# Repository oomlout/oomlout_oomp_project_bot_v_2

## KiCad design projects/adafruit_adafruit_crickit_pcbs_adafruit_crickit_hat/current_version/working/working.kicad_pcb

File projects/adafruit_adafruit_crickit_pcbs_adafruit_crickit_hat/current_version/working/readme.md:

# adafruit_crickit_pcbs
 
## summary 
* id: adafruit_adafruit_crickit_pcbs_adafruit_crickit_hat
* user: adafruit
* name: adafruit_crickit_pcbs
* board: adafruit_crickit_hat
* repo: https://github.com/adafruit/Adafruit_Crickit_PCBs

* src_file_repo_sch: 
* src_file_repo_sch_link: https://github.com/adafruit/Adafruit_Crickit_PCBs/tree/master/
* full details link: https://github.com/oomlout/oomlout_oomp_project_bot_v_2/tree/main/projects/adafruit_adafruit_crickit_pcbs_adafruit_crickit_hat/current_version/working  

## schematic  
  
[schematic (pdf)](working_schematic.pdf) 

## pcb  

[board (pdf)](working.pdf)  

## working_bom
| Id | Designator | Footprint | Quantity | Designation | Supplier and ref |  | None | 
| --- | --- | --- | --- | --- | --- | --- | --- | 
| 1 | C12,C6,C20,C22,C11,C18 | 0805-NO | 6 | 0.1uF |  |  | [''] | 
| 2 | JP8 | TERMBLOC_1X5-3.5MM | 1 | 5pin 3.5mm |  |  | [''] | 
| 3 | R9,R10 | 0603-NO | 2 | 1Mohm |  |  | [''] | 
| 4 | TP31,TP30,TP32,TP29 | PCB_ALLI | 4 | SEWTAPPCB_ALLIGATOR |  |  | [''] | 
| 5 | SPKR0 | TERMBLOCK_1X2-3.5MM | 1 | 3.5mm |  |  | [''] | 
| 6 | R16,R17,R11,R8,R1 | 0603-NO | 5 | 264K |  |  | [''] | 
| 7 | R12,R13 | 0805-NO | 2 | 100 |  |  | [''] | 
| 8 | POWERFAIL0 | CHIPLED_0805_NOOUTLINE | 1 | red |  |  | [''] | 
| 9 | VR2 | TRIMPOT_BOURNS_3303W | 1 | 10K trim |  |  | [''] | 
| 10 | POWEROK0 | CHIPLED_0805_NOOUTLINE | 1 | green |  |  | [''] | 
| 11 | MS2 | FEATHERWING_SMT2 | 1 | FEATHERWING_SMTDUAL |  |  | [''] | 
| 12 | CN1 | 4UCONN_20329_V2 | 1 | 4U#20329 |  |  | [''] | 
| 13 | C10 | PANASONIC_C | 1 | 47uF+/16v |  |  | [''] | 
| 14 | R7,R2,R5,R18,R6,R15 | 0603-NO | 6 | 2.2K |  |  | [''] | 
| 15 | U2 | HTSSOP16 | 1 | DRV8833PWPR |  |  | [''] | 
| 16 | U$41,U$50,U$49,U$52,U$44,U$43,U$42,U$51 | MOUNTINGHOLE_3.0_NPH | 8 | MOUNTINGHOLE3.0_NPH |  |  | [''] | 
| 17 | FB1 | 0805-NO | 1 | Ferrite |  |  | [''] | 
| 18 | C17,C19,C7,C15,C2,C16,C21 | 0805-NO | 7 | 10uF |  |  | [''] | 
| 19 | IC4 | WSON8 | 1 | TPS259573 |  |  | [''] | 
| 20 | C8 | 0603-NO | 1 | DNP |  |  | [''] | 
| 21 | C3 | 0805_10MGAP | 1 | 1uF |  |  | [''] | 
| 22 | Q2 | POWERDI3333 | 1 | AON7401 |  |  | [''] | 
| 23 | R4,R3 | _1206 | 2 | 0.2Î© |  |  | [''] | 
| 24 | U5 | MSOP8_0.65MM | 1 | PAM8302AASCR |  |  | [''] | 
| 25 | JP2 | TERMBLOC_1X5-3.5MM | 1 | 3.5mm |  |  | [''] | 
| 26 | D1,D2 | SOD-323 | 2 | 1N4148 |  |  | [''] | 
| 27 | C13,C14 | 0805-NO | 2 | 1uF |  |  | [''] | 
| 28 | FID1,FID3,FID2 | FIDUCIAL_1MM | 3 | FIDUCIAL_1MM |  |  | [''] | 
| 29 | X2 | DCJACK_2MM_PTH | 1 | 2.1mm DC |  |  | [''] | 
| 30 | JP5 | 1X01_ROUND | 1 |  |  |  | [''] | 
| 31 | IC2 | SO16 | 1 | ULN2003AD |  |  | [''] | 
| 32 | L0 | CHIPLED_0805_NOOUTLINE | 1 | yellow |  |  | [''] | 
| 33 | C5 | 0805-NO | 1 | 10ÂµF |  |  | [''] | 
| 34 | ON/OFF0 | EG1390 | 1 | MSS-22C01G2 |  |  | [''] | 
| 35 | SJ1 | SOLDERJUMPER_CLOSEDWIRE | 1 |  |  |  | [''] | 
| 36 | LED1 | LED3535 | 1 | WS2812B3535 |  |  | [''] | 
| 37 | GPIO0 | 3X08 | 1 | 3x8 FEMALE |  |  | [''] | 
| 38 | JP3 | 1X16_ROUND | 1 |  |  |  | [''] | 
| 39 | U$4 | TQFN48_7MM | 1 | ATSAMD21G_QFN |  |  | [''] | 
| 40 | IC3 | SOT23-5 | 1 | 74AHCT1G125DBV |  |  | [''] | 
| 41 | U$74 | CRICKIT_WING_TOP | 1 |  |  |  | [''] | 
| 42 | SERVO0 | 3X04 | 1 | 3x4 Male |  |  | [''] | 
| 43 | C4,C1 | 0805-NO | 2 | 10ÂµF/16V |  |  | [''] | 
| 44 | JP1 | 1X02_ROUND | 1 |  |  |  | [''] | 
| 45 | C9 | PANASONIC_C | 1 | 47uF/16v |  |  | [''] | 
| 46 | R14 | 0603-NO | 1 | 510 |  |  | [''] | 
| 47 | U1 | SOT23-5 | 1 | mic5225-3.3 |  |  | [''] | 
| 48 | SW1 | EVQ-Q2_SMALLER | 1 | EVQQ2 |  |  | [''] | 
| 49 | JP4 | 1X12_ROUND | 1 |  |  |  | [''] | 
| 50 | NEOPIX0 | TERMBLOCK_1X3-3.5MM | 1 | 3.5mm |  |  | [''] | 
| 51 | SJ8 | SOLDERJUMPER_ARROW_NOPASTE | 1 | ISENSEB |  |  | [''] | 
| 52 | TP3,TP1,TP2 | TP15R | 3 | TPTP15R |  |  | [''] | 
| 53 | U$72 | CRICKIT_WING_BOT | 1 |  |  |  | [''] | 
| 54 | U$76 | PCBFEAT-REV-040 | 1 |  |  |  | [''] | 
| 55 | SJ7 | SOLDERJUMPER_ARROW_NOPASTE | 1 | ISENSEA |  |  | [''] | 

## bom_schematic
no data

## mounting_holes
| x | y | package | value | ref | size | 
| --- | --- | --- | --- | --- | --- | 
| 21.59 | 0.0 | MOUNTINGHOLE_3.0_NPH | MOUNTINGHOLE3.0_NPH | U$41 | m3 | 
| 53.85 | 0.0 | MOUNTINGHOLE_3.0_NPH | MOUNTINGHOLE3.0_NPH | U$42 | m3 | 
| 0.0 | 21.59 | MOUNTINGHOLE_3.0_NPH | MOUNTINGHOLE3.0_NPH | U$43 | m3 | 
| 75.44 | 21.59 | MOUNTINGHOLE_3.0_NPH | MOUNTINGHOLE3.0_NPH | U$44 | m3 | 
| 75.44 | 53.85 | MOUNTINGHOLE_3.0_NPH | MOUNTINGHOLE3.0_NPH | U$49 | m3 | 
| 0.0 | 53.85 | MOUNTINGHOLE_3.0_NPH | MOUNTINGHOLE3.0_NPH | U$50 | m3 | 
| 21.59 | 75.44 | MOUNTINGHOLE_3.0_NPH | MOUNTINGHOLE3.0_NPH | U$51 | m3 | 
| 53.85 | 75.44 | MOUNTINGHOLE_3.0_NPH | MOUNTINGHOLE3.0_NPH | U$52 | m3 |

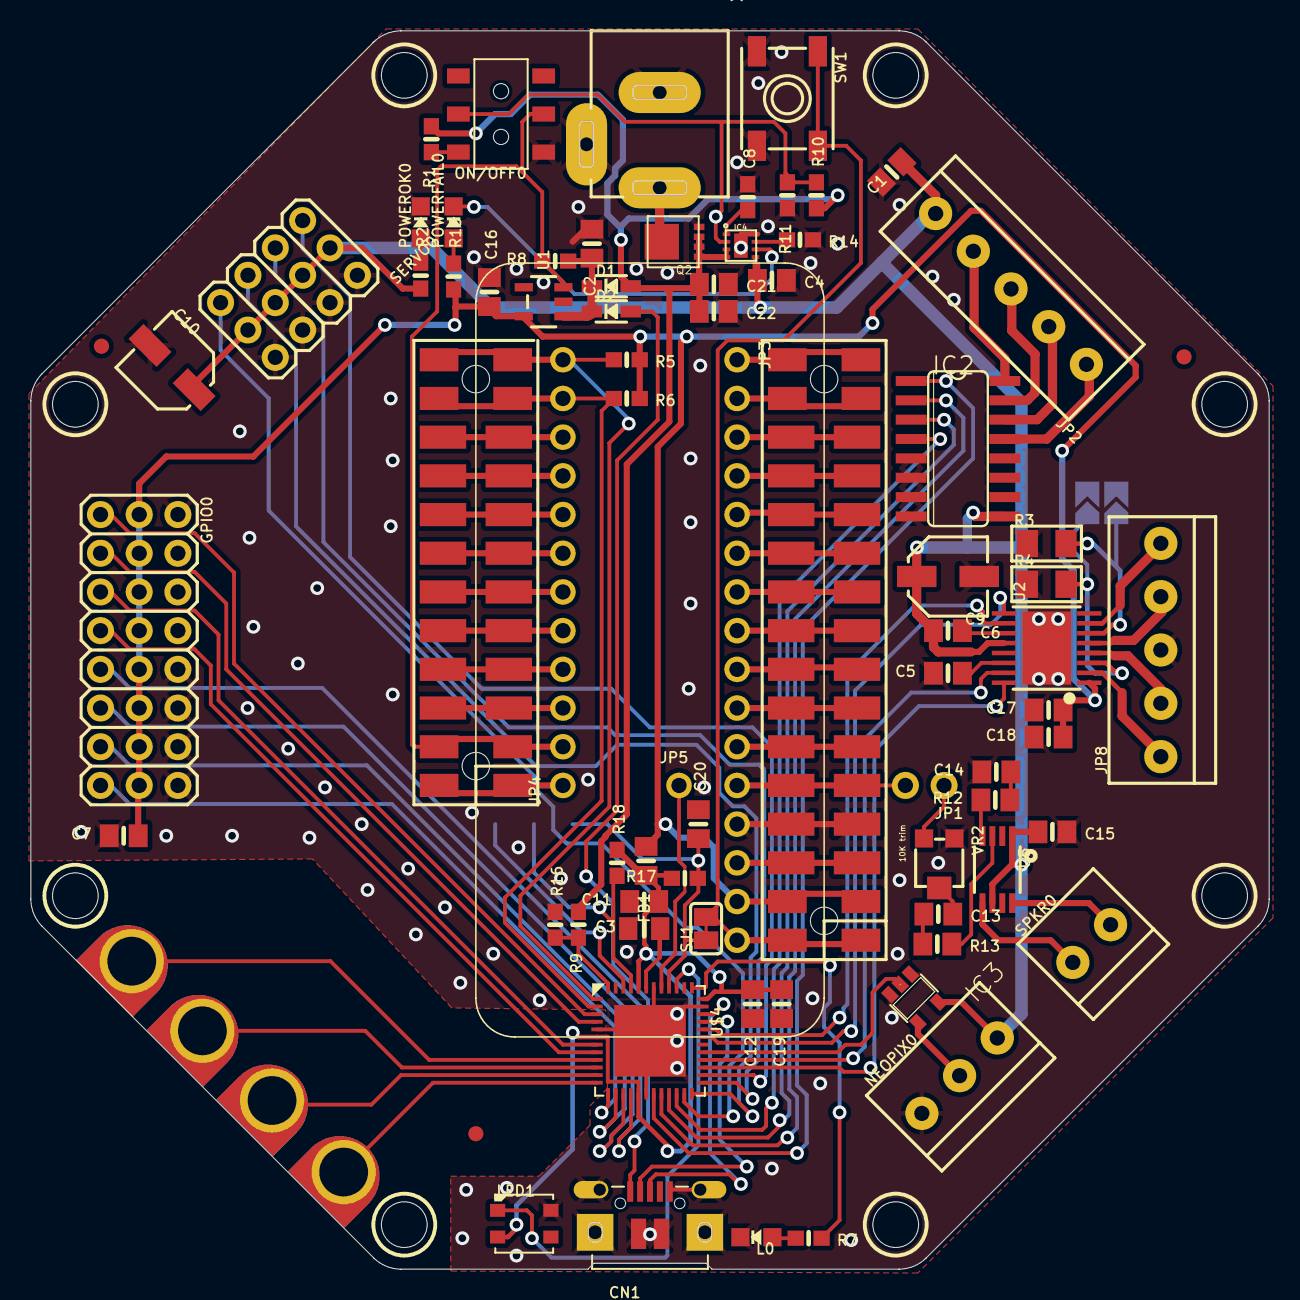
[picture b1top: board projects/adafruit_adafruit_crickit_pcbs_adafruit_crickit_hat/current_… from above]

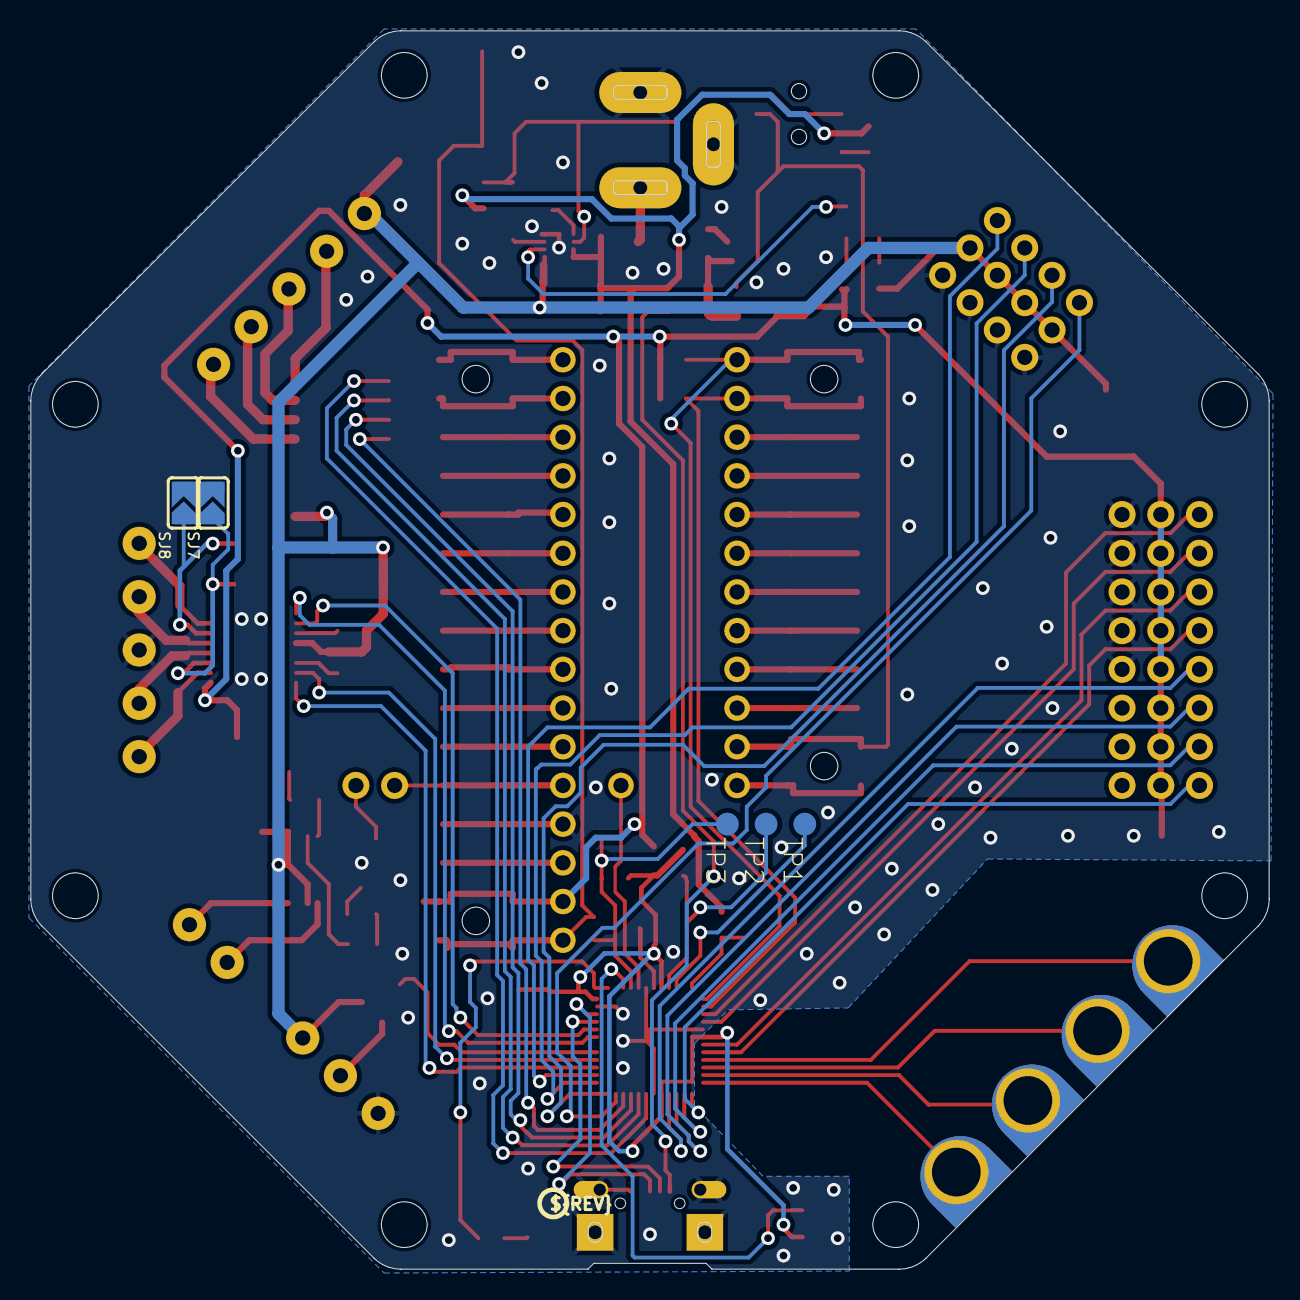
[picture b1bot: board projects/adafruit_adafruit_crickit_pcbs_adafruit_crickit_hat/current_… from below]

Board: 16 copper layers, 81.3 x 81.3 mm, 95 parts (7 on the bottom side), 98 nets.

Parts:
C1, C4: 10µF/16V; 0805-NO
C2, C7, C15, C16, C17, C19, C21: 10uF; 0805-NO
C3: 1uF; 0805_10MGAP
C5: 10µF; 0805-NO
C6, C11, C12, C18, C20, C22: 0.1uF; 0805-NO
C8: DNP; 0603-NO
C9: 47uF/16v; PANASONIC_C
C10: 47uF+/16v; PANASONIC_C
C13, C14: 1uF; 0805-NO
CN1: 4U#20329; 4UCONN_20329_V2
D1, D2: 1N4148; SOD-323
FB1: Ferrite; 0805-NO
FID1, FID2, FID3: FIDUCIAL_1MM
GPIO0: 3x8 FEMALE; 3X08
IC2: ULN2003AD; SO16
IC3: 74AHCT1G125DBV; SOT23-5
IC4: TPS259573; WSON8
JP1: 1X02_ROUND
JP2: 3.5mm; TERMBLOC_1X5-3.5MM
JP3: 1X16_ROUND
JP4: 1X12_ROUND
JP5: 1X01_ROUND
JP8: 5pin 3.5mm; TERMBLOC_1X5-3.5MM
L0: yellow; CHIPLED_0805_NOOUTLINE
LED1: WS2812B3535; LED3535
MS2: FEATHERWING_SMTDUAL; FEATHERWING_SMT2
NEOPIX0: 3.5mm; TERMBLOCK_1X3-3.5MM
ON/OFF0: MSS-22C01G2; EG1390
POWERFAIL0: red; CHIPLED_0805_NOOUTLINE
POWEROK0: green; CHIPLED_0805_NOOUTLINE
Q2: AON7401; POWERDI3333
R1, R8, R11, R16, R17: 264K; 0603-NO
R2, R5, R6, R7, R15, R18: 2.2K; 0603-NO
R3, R4: 0.2Ω; _1206
R9, R10: 1Mohm; 0603-NO
R12, R13: 100; 0805-NO
R14: 510; 0603-NO
SERVO0: 3x4 Male; 3X04
SJ1: SOLDERJUMPER_CLOSEDWIRE
SJ7: ISENSEA; SOLDERJUMPER_ARROW_NOPASTE
SJ8: ISENSEB; SOLDERJUMPER_ARROW_NOPASTE
SPKR0: 3.5mm; TERMBLOCK_1X2-3.5MM
SW1: EVQQ2; EVQ-Q2_SMALLER
TP1, TP2, TP3: TPTP15R; TP15R
TP29, TP30, TP31, TP32: SEWTAPPCB_ALLIGATOR; PCB_ALLI
U1: mic5225-3.3; SOT23-5
U2: DRV8833PWPR; HTSSOP16
U5: PAM8302AASCR; MSOP8_0.65MM
U$4: ATSAMD21G_QFN; TQFN48_7MM
U$41, U$42, U$43, U$44, U$49, U$50, U$51, U$52: MOUNTINGHOLE3.0_NPH; MOUNTINGHOLE_3.0_NPH
U$72: CRICKIT_WING_BOT
U$74: CRICKIT_WING_TOP
U$76: PCBFEAT-REV-040
VR2: 10K trim; TRIMPOT_BOURNS_3303W
X2: 2.1mm DC; DCJACK_2MM_PTH

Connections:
3.3V: C7.1, C16.1, C17.1, C18.1, FB1.1, GPIO0.2, GPIO0.5, GPIO0.8, GPIO0.11, GPIO0.14, GPIO0.17, GPIO0.20, GPIO0.23, JP3.15, MS2.2, MS2.2', R5.2, R6.2, R15.1, U1.5, U2.1
5.0V: C1.1, C4.1, C6.1, C9.+, C10.+, C15.1, IC2.9, IC3.5, IC4.5, JP2.P5, NEOPIX0.1, R2.1, SERVO0.2, SERVO0.5, SERVO0.8, SERVO0.11, U2.12, U5.1, U5.6
ANALOG1: GPIO0.1, U$4.3
ANALOG2: GPIO0.4, U$4.4
ANALOG3: GPIO0.7, U$4.7
ANALOG4: GPIO0.10, U$4.8
ANALOG5: GPIO0.13, U$4.16
ANALOG6: GPIO0.16, U$4.15
ANALOG7: GPIO0.19, U$4.14
ANALOG8: GPIO0.22, U$4.13
AOUT3: JP8.P1, U2.2
AOUT4: JP8.P2, U2.4
AREF: JP3.14, MS2.3, MS2.3'
AUDIO: JP1.1, VR2.3
AUDIO_OUT: JP1.2, JP3.12, MS2.5, MS2.5'
B: JP3.11, MS2.6, MS2.6'
C: JP3.10, MS2.7, MS2.7'
CAPTOUCH1: TP30.P$1, U$4.9
CAPTOUCH2: TP32.P$1, U$4.10
CAPTOUCH3: TP29.P$1, U$4.11
CAPTOUCH4: TP31.P$1, U$4.12
D: JP3.9, MS2.8, MS2.8'
D+: CN1.D+, U$4.34
D-: CN1.D-, U$4.33
DRIVEIN1: IC2.1, U$4.19
DRIVEIN2: IC2.2, U$4.20
DRIVEIN3: IC2.3, U$4.21
DRIVEIN4: IC2.4, U$4.22
DRIVEOUT1: IC2.16, JP2.P4
DRIVEOUT2: IC2.15, JP2.P3
DRIVEOUT3: IC2.14, JP2.P2
DRIVEOUT4: IC2.13, JP2.P1
E: JP3.8, MS2.9, MS2.9'
ENABLE: JP4.2, MS2.27, MS2.27', ON/OFF0.P2, R8.2, U1.3
F: JP3.7, MS2.10, MS2.10'
G: JP3.1, MS2.16, MS2.16'
GND: C1.2, C2.1, C3.2, C4.2, C5.2, C7.2, C8.2, C9.-, C10.-, C11.2, C12.2, C14.2, C15.2, C16.2, C17.2, C18.2, C19.2, C20.2, C21.2, C22.2, CN1.BASE@1, CN1.BASE@2, CN1.GND, CN1.SPRT@1, CN1.SPRT@2, CN1.SPRT@3, CN1.SPRT@4, GPIO0.3, GPIO0.6, GPIO0.9, GPIO0.12, GPIO0.15, GPIO0.18, GPIO0.21, GPIO0.24, IC2.5, IC2.6, IC2.7, IC2.8, IC3.1, IC3.3, IC4.8, IC4.PAD, JP3.13, JP8.P3, L0.C, LED1.4, MS2.4, MS2.4', NEOPIX0.3, ON/OFF0.O2, POWEROK0.C, Q2.4, R3.1, R4.1, R11.2, R14.2, R16.2, SERVO0.3, SERVO0.6, SERVO0.9, SERVO0.12, SJ7.2, SJ8.2, SW1.A, SW1.A', U1.2, U2.13, U2.PPAD, U5.7, U$4.5, U$4.18, U$4.35, U$4.42, U$4.THERMAL, VR2.1, X2.GND, X2.GNDBREAK
INT_NEO: LED1.1, U$4.39
IRQ: JP5.1, U$4.41
L: JP4.6, MS2.23, MS2.23'
LED: R7.2, U$4.37
M: JP4.5, MS2.24, MS2.24'
M1_ASEN: R4.2, SJ7.1, U2.3
M1_BSEN: R3.2, SJ8.1, U2.6
M1_VINT: C5.1, U2.14
MISO: JP3.4, MS2.13, MS2.13'
MOSI: JP3.5, MS2.12, MS2.12'
MOTOR_AIN1: U2.16, U$4.27
MOTOR_AIN2: U2.15, U$4.28
MOTOR_BIN1: U2.9, U$4.31
MOTOR_BIN2: U2.10, U$4.32
N: JP4.4, MS2.25, MS2.25'
unnamed: C6.2, U2.11
unnamed: C2.2, D1.C, D2.C, R8.1, U1.1
unnamed: IC3.4, NEOPIX0.2
unnamed: ON/OFF0.O1, R1.2
unnamed: L0.A, R7.1
unnamed: JP4.7, MS2.22, MS2.22'
unnamed: JP4.8, MS2.21, MS2.21'
unnamed: IC4.7, R14.1
unnamed: JP4.9, MS2.20, MS2.20'
unnamed: JP4.10, MS2.19, MS2.19'
unnamed: POWERFAIL0.A, R15.2
unnamed: IC4.6, POWERFAIL0.C
unnamed: C8.1, IC4.1
unnamed: JP8.P5, U2.7
unnamed: POWEROK0.A, R2.2
unnamed: JP8.P4, U2.5
unnamed: R12.2, U5.4
unnamed: R13.2, U5.3
unnamed: C14.1, R12.1
unnamed: C13.1, R13.1
unnamed: C13.2, VR2.2
NEOPIXEL: IC3.2, U$4.29
PWR: Q2.5678, X2.PWR
RX: JP3.3, MS2.14, MS2.14'
SCL: JP4.11, MS2.18, MS2.18', R6.1, U$4.2
SCLK: JP3.6, MS2.11, MS2.11'
SDA: JP4.12, MS2.17, MS2.17', R5.1, U$4.1
SEESAW_RESET: C20.1, R17.1, SJ1.1, TP3.TP, U$4.40
SERVO1: SERVO0.1, U$4.26
SERVO2: SERVO0.4, U$4.25
SERVO3: SERVO0.7, U$4.24
SERVO4: SERVO0.10, U$4.23
SPKR+: SPKR0.2, U5.5
SPKR-: SPKR0.1, U5.8
SWCLK: R18.1, TP2.TP, U$4.45
SWDIO: TP1.TP, U$4.46
TX: JP3.2, MS2.15, MS2.15'
USB: JP4.3, MS2.26, MS2.26'
VBAT: JP4.1, MS2.28, MS2.28'
VBUS: CN1.VBUS, D2.A
VDD: C11.1, C12.1, C19.1, FB1.2, LED1.2, R17.2, R18.2, U$4.6, U$4.17, U$4.36, U$4.44
VDDCORE: C3.1, U$4.43
VIN: C21.1, C22.1, D1.A, IC4.3, IC4.4, Q2.1, Q2.2, Q2.3, R1.1, R9.1, R10.1
VIN_SENSE: R9.2, R16.1, U$4.48
~RESET: JP3.16, MS2.1, MS2.1', SJ1.2, SW1.B, SW1.B'
~TPSEN: IC4.2, ON/OFF0.P1, R10.2, R11.1

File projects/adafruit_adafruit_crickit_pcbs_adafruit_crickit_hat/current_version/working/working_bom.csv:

"Id";"Designator";"Footprint";"Quantity";"Designation";"Supplier and ref";
1;"C12,C6,C20,C22,C11,C18";"0805-NO";6;"0.1uF";;;
2;"JP8";"TERMBLOC_1X5-3.5MM";1;"5pin 3.5mm";;;
3;"R9,R10";"0603-NO";2;"1Mohm";;;
4;"TP31,TP30,TP32,TP29";"PCB_ALLI";4;"SEWTAPPCB_ALLIGATOR";;;
5;"SPKR0";"TERMBLOCK_1X2-3.5MM";1;"3.5mm";;;
6;"R16,R17,R11,R8,R1";"0603-NO";5;"264K";;;
7;"R12,R13";"0805-NO";2;"100";;;
8;"POWERFAIL0";"CHIPLED_0805_NOOUTLINE";1;"red";;;
9;"VR2";"TRIMPOT_BOURNS_3303W";1;"10K trim";;;
10;"POWEROK0";"CHIPLED_0805_NOOUTLINE";1;"green";;;
11;"MS2";"FEATHERWING_SMT2";1;"FEATHERWING_SMTDUAL";;;
12;"CN1";"4UCONN_20329_V2";1;"4U#20329";;;
13;"C10";"PANASONIC_C";1;"47uF+/16v";;;
14;"R7,R2,R5,R18,R6,R15";"0603-NO";6;"2.2K";;;
15;"U2";"HTSSOP16";1;"DRV8833PWPR";;;
16;"U$41,U$50,U$49,U$52,U$44,U$43,U$42,U$51";"MOUNTINGHOLE_3.0_NPH";8;"MOUNTINGHOLE3.0_NPH";;;
17;"FB1";"0805-NO";1;"Ferrite";;;
18;"C17,C19,C7,C15,C2,C16,C21";"0805-NO";7;"10uF";;;
19;"IC4";"WSON8";1;"TPS259573";;;
20;"C8";"0603-NO";1;"DNP";;;
21;"C3";"0805_10MGAP";1;"1uF";;;
22;"Q2";"POWERDI3333";1;"AON7401";;;
23;"R4,R3";"_1206";2;"0.2Ω";;;
24;"U5";"MSOP8_0.65MM";1;"PAM8302AASCR";;;
25;"JP2";"TERMBLOC_1X5-3.5MM";1;"3.5mm";;;
26;"D1,D2";"SOD-323";2;"1N4148";;;
27;"C13,C14";"0805-NO";2;"1uF";;;
28;"FID1,FID3,FID2";"FIDUCIAL_1MM";3;"FIDUCIAL_1MM";;;
29;"X2";"DCJACK_2MM_PTH";1;"2.1mm DC";;;
30;"JP5";"1X01_ROUND";1;"";;;
31;"IC2";"SO16";1;"ULN2003AD";;;
32;"L0";"CHIPLED_0805_NOOUTLINE";1;"yellow";;;
33;"C5";"0805-NO";1;"10µF";;;
34;"ON/OFF0";"EG1390";1;"MSS-22C01G2";;;
35;"SJ1";"SOLDERJUMPER_CLOSEDWIRE";1;"";;;
36;"LED1";"LED3535";1;"WS2812B3535";;;
37;"GPIO0";"3X08";1;"3x8 FEMALE";;;
38;"JP3";"1X16_ROUND";1;"";;;
39;"U$4";"TQFN48_7MM";1;"ATSAMD21G_QFN";;;
40;"IC3";"SOT23-5";1;"74AHCT1G125DBV";;;
41;"U$74";"CRICKIT_WING_TOP";1;"";;;
42;"SERVO0";"3X04";1;"3x4 Male";;;
43;"C4,C1";"0805-NO";2;"10µF/16V";;;
44;"JP1";"1X02_ROUND";1;"";;;
45;"C9";"PANASONIC_C";1;"47uF/16v";;;
46;"R14";"0603-NO";1;"510";;;
47;"U1";"SOT23-5";1;"mic5225-3.3";;;
48;"SW1";"EVQ-Q2_SMALLER";1;"EVQQ2";;;
49;"JP4";"1X12_ROUND";1;"";;;
50;"NEOPIX0";"TERMBLOCK_1X3-3.5MM";1;"3.5mm";;;
51;"SJ8";"SOLDERJUMPER_ARROW_NOPASTE";1;"ISENSEB";;;
52;"TP3,TP1,TP2";"TP15R";3;"TPTP15R";;;
53;"U$72";"CRICKIT_WING_BOT";1;"";;;
54;"U$76";"PCBFEAT-REV-040";1;"";;;
55;"SJ7";"SOLDERJUMPER_ARROW_NOPASTE";1;"ISENSEA";;;

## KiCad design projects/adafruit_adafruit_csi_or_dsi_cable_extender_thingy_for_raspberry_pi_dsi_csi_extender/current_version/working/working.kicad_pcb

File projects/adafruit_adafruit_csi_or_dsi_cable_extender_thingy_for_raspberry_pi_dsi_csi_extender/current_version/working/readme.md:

# adafruit_csi_or_dsi_cable_extender_thingy_for_raspberry_pi
 
## summary 
* id: adafruit_adafruit_csi_or_dsi_cable_extender_thingy_for_raspberry_pi_dsi_csi_extender
* user: adafruit
* name: adafruit_csi_or_dsi_cable_extender_thingy_for_raspberry_pi
* board: dsi_csi_extender
* repo: https://github.com/adafruit/Adafruit-CSI-or-DSI-Cable-Extender-Thingy-for-Raspberry-Pi

* src_file_repo_sch: 
* src_file_repo_sch_link: https://github.com/adafruit/Adafruit-CSI-or-DSI-Cable-Extender-Thingy-for-Raspberry-Pi/tree/master/
* full details link: https://github.com/oomlout/oomlout_oomp_project_bot_v_2/tree/main/projects/adafruit_adafruit_csi_or_dsi_cable_extender_thingy_for_raspberry_pi_dsi_csi_extender/current_version/working  

## schematic  
  
[schematic (pdf)](working_schematic.pdf) 

## pcb  

[board (pdf)](working.pdf)  

## working_bom
| Id | Designator | Footprint | Quantity | Designation | Supplier and ref |  | None | 
| --- | --- | --- | --- | --- | --- | --- | --- | 
| 1 | FID1,FID2 | FIDUCIAL_1MM | 2 | FIDUCIAL_1MM |  |  | [''] | 
| 2 | U$3,U$2 | MOUNTINGHOLE_2.5_PLATED | 2 | MOUNTINGHOLE2.5 |  |  | [''] | 
| 3 | U$4 | ADAFRUIT_2.5MM | 1 |  |  |  | [''] | 
| 4 | JP1,JP2 | FPC_15PIN_1.0MM | 2 |  |  |  | [''] | 
| 5 | U$6 | PCBFEAT-REV-040 | 1 |  |  |  | [''] | 
| 6 | U$5 | ADAFRUIT_5MM | 1 |  |  |  | [''] | 

## bom_schematic
| Ref | Qnty | Value | Cmp name | Footprint | Description | Vendor | DNP | 
| --- | --- | --- | --- | --- | --- | --- | --- | 
| FID1, FID2 | 2 | FIDUCIAL_1MM | FIDUCIAL_1MM | working:FIDUCIAL_1MM |  |  |  | 
| JP1, JP2 | 2 | HEADER-1X15_FPC1MM_PI | HEADER-1X15_FPC1MM_PI | working:FPC_15PIN_1.0MM |  |  |  | 
| U$2, U$3 | 2 | MOUNTINGHOLE2.5 | MOUNTINGHOLE2.5 | working:MOUNTINGHOLE_2.5_PLATED |  |  |  | 

## mounting_holes
| x | y | package | value | ref | size | 
| --- | --- | --- | --- | --- | --- | 
| 0.0 | 0.0 | MOUNTINGHOLE_2.5_PLATED | MOUNTINGHOLE2.5 | U$2 | m3 | 
| 20.32 | 0.0 | MOUNTINGHOLE_2.5_PLATED | MOUNTINGHOLE2.5 | U$3 | m3 |

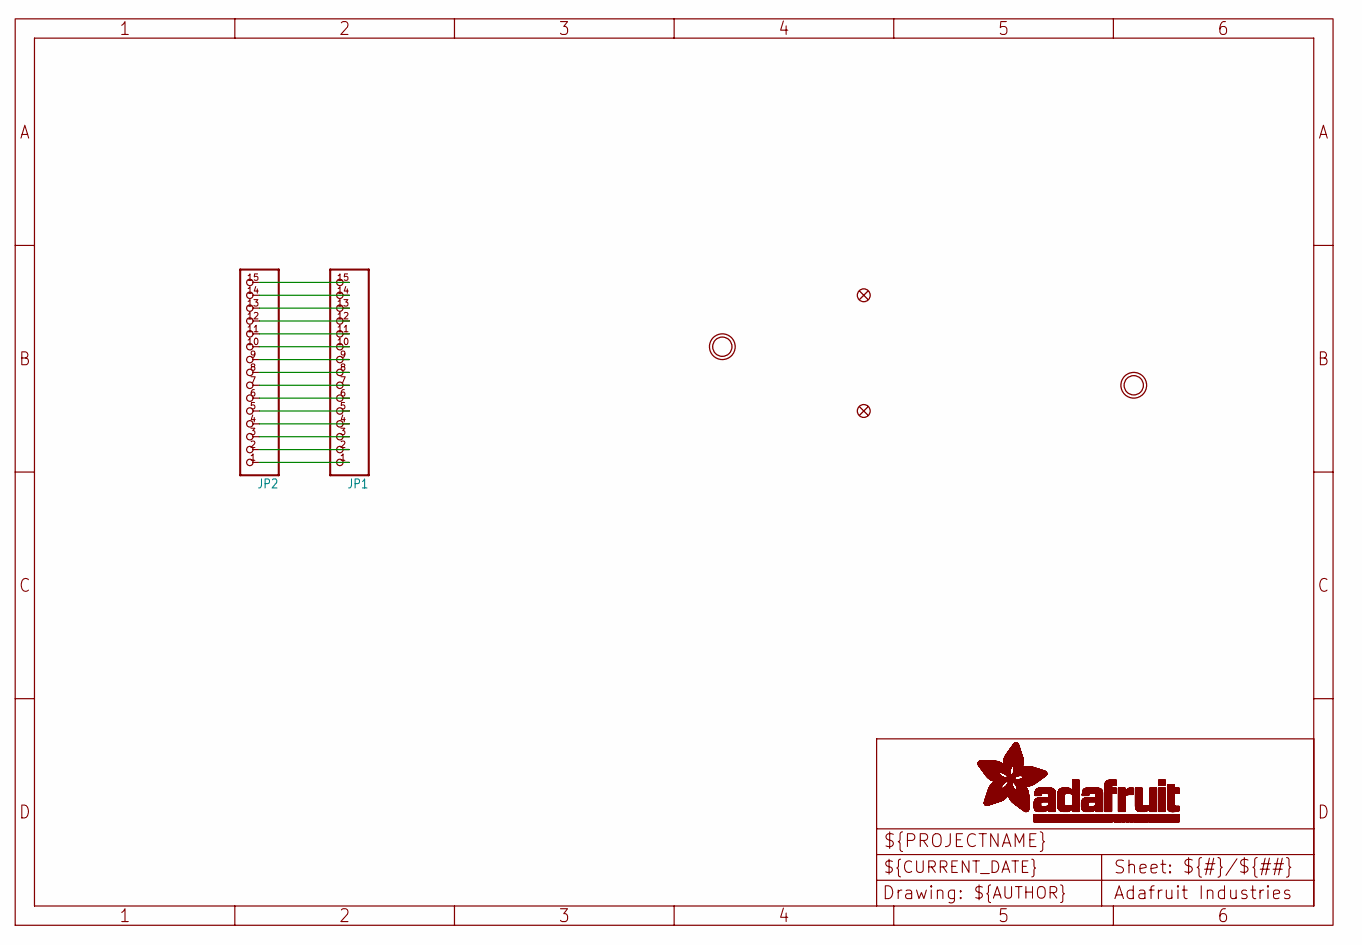
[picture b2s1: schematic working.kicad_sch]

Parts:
FID1, FID2: FIDUCIAL_1MM
JP1, JP2: HEADER-1X15_FPC1MM_PI; FPC_15PIN_1.0MM
U$2, U$3: MOUNTINGHOLE2.5; MOUNTINGHOLE_2.5_PLATED

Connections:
unnamed: JP1.1, JP2.1
unnamed: JP1.2, JP2.2
unnamed: JP1.3, JP2.3
unnamed: JP1.4, JP2.4
unnamed: JP1.5, JP2.5
unnamed: JP1.6, JP2.6
unnamed: JP1.7, JP2.7
unnamed: JP1.8, JP2.8
unnamed: JP1.9, JP2.9
unnamed: JP1.10, JP2.10
unnamed: JP1.11, JP2.11
unnamed: JP1.12, JP2.12
unnamed: JP1.13, JP2.13
unnamed: JP1.14, JP2.14
unnamed: JP1.15, JP2.15

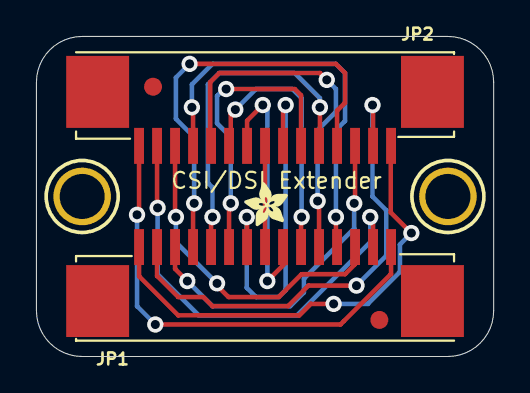
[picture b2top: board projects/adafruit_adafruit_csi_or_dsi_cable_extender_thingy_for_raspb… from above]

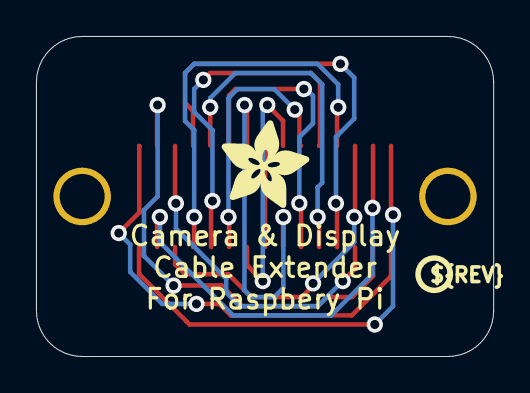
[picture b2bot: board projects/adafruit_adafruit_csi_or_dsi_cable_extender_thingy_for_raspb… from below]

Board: 2 copper layers, 25.4 x 17.8 mm, 9 parts (2 on the bottom side), 15 nets.

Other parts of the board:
U$4: ADAFRUIT_2.5MM
U$5: ADAFRUIT_5MM
U$6: PCBFEAT-REV-040

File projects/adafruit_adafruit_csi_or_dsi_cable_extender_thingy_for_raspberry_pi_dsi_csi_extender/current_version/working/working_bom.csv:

"Id";"Designator";"Footprint";"Quantity";"Designation";"Supplier and ref";
1;"FID1,FID2";"FIDUCIAL_1MM";2;"FIDUCIAL_1MM";;;
2;"U$3,U$2";"MOUNTINGHOLE_2.5_PLATED";2;"MOUNTINGHOLE2.5";;;
3;"U$4";"ADAFRUIT_2.5MM";1;"";;;
4;"JP1,JP2";"FPC_15PIN_1.0MM";2;"";;;
5;"U$6";"PCBFEAT-REV-040";1;"";;;
6;"U$5";"ADAFRUIT_5MM";1;"";;;

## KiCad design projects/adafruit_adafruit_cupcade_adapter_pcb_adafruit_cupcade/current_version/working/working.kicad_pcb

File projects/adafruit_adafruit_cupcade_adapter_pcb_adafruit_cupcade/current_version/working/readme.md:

# adafruit_cupcade_adapter_pcb
 
## summary 
* id: adafruit_adafruit_cupcade_adapter_pcb_adafruit_cupcade
* user: adafruit
* name: adafruit_cupcade_adapter_pcb
* board: adafruit_cupcade
* repo: https://github.com/adafruit/Adafruit-Cupcade-Adapter-PCB

* src_file_repo_sch: 
* src_file_repo_sch_link: https://github.com/adafruit/Adafruit-Cupcade-Adapter-PCB/tree/master/
* full details link: https://github.com/oomlout/oomlout_oomp_project_bot_v_2/tree/main/projects/adafruit_adafruit_cupcade_adapter_pcb_adafruit_cupcade/current_version/working  

## schematic  
  
[schematic (pdf)](working_schematic.pdf) 

## pcb  

[board (pdf)](working.pdf)  

## working_bom
| Id | Designator | Footprint | Quantity | Designation | Supplier and ref |  | None | 
| --- | --- | --- | --- | --- | --- | --- | --- | 
| 1 | R1,R4,R5,R2,R3 | 0805-NO | 5 | 10K |  |  | [''] | 
| 2 | C1 | PANASONIC_C | 1 | 100uF |  |  | [''] | 
| 3 | AUDIO0 | 1X03_OVAL | 1 |  |  |  | [''] | 
| 4 | IC1 | SO14 | 1 | LM339D |  |  | [''] | 
| 5 | U$2,U$3 | MOUNTINGHOLE_2.5_PLATED | 2 | MOUNTINGHOLE2.5 |  |  | [''] | 
| 6 | IC2 | SO08 | 1 | TS922 |  |  | [''] | 
| 7 | BUTTON_CREDIT0,BUTTON_START0,BUTTON_B0,BUTTON_A0 | 1X02_OVAL | 4 |  |  |  | [''] | 
| 8 | FID1,FID2,FID3 | FIDUCIAL_1MM | 3 | FIDUCIAL" |  |  | [''] | 
| 9 | C2 | 0805-NO | 1 | 10uF |  |  | [''] | 
| 10 | JP1 | RASBERRYPI_IDC | 1 |  |  |  | [''] | 
| 11 | SPEAKER0 | 1X02_OVAL | 1 | 8Ohm |  |  | [''] | 
| 12 | C3 | 0805-NO | 1 | 0.1uF |  |  | [''] | 
| 13 | JOYSTICK0 | 1X05_OVAL | 1 |  |  |  | [''] | 
| 14 | U$1 | DRAGON_300MIL | 1 |  |  |  | [''] | 

## bom_schematic
| Ref | Qnty | Value | Cmp name | Footprint | Description | Vendor | DNP | 
| --- | --- | --- | --- | --- | --- | --- | --- | 
| AUDIO0 | 1 | HEADER-1X3 | HEADER-1X3 | working:1X03_OVAL |  |  |  | 
| BUTTON_A0 | 1 | HEADER-1X2 | HEADER-1X2 | working:1X02_OVAL |  |  |  | 
| BUTTON_B0 | 1 | HEADER-1X2 | HEADER-1X2 | working:1X02_OVAL |  |  |  | 
| BUTTON_CREDIT0 | 1 | HEADER-1X2 | HEADER-1X2 | working:1X02_OVAL |  |  |  | 
| BUTTON_START0 | 1 | HEADER-1X2 | HEADER-1X2 | working:1X02_OVAL |  |  |  | 
| C1 | 1 | 100uF | CAP_ELECTROLYTICPANASONIC_C | working:PANASONIC_C |  |  |  | 
| C2 | 1 | 10uF | CAP_CERAMIC0805-NOOUTLINE | working:0805-NO |  |  |  | 
| C3 | 1 | 0.1uF | CAP_CERAMIC0805-NOOUTLINE | working:0805-NO |  |  |  | 
| FID1, FID2, FID3 | 3 | FIDUCIAL"" | FIDUCIAL{dblquote}{dblquote} | working:FIDUCIAL_1MM |  |  |  | 
| IC1 | 1 | LM339D | LM339D | working:SO14 |  |  |  | 
| IC2 | 1 | TL072D | TL072D | working:SO08 |  |  |  | 
| JOYSTICK0 | 1 | HEADER-1X5 | HEADER-1X5 | working:1X05_OVAL |  |  |  | 
| JP1 | 1 | RASBERRYPI_IDC | RASBERRYPI_IDC | working:RASBERRYPI_IDC |  |  |  | 
| R1, R2, R3, R4, R5 | 5 | 10K | RESISTOR0805_NOOUTLINE | working:0805-NO |  |  |  | 
| SPEAKER0 | 1 | 8Ohm | HEADER-1X2 | working:1X02_OVAL |  |  |  | 
| U$2, U$3 | 2 | MOUNTINGHOLE2.5 | MOUNTINGHOLE2.5 | working:MOUNTINGHOLE_2.5_PLATED |  |  |  | 

## mounting_holes
| x | y | package | value | ref | size | 
| --- | --- | --- | --- | --- | --- | 
| 0.0 | 0.0 | MOUNTINGHOLE_2.5_PLATED | MOUNTINGHOLE2.5 | U$2 | m3 | 
| 0.0 | 35.56 | MOUNTINGHOLE_2.5_PLATED | MOUNTINGHOLE2.5 | U$3 | m3 |

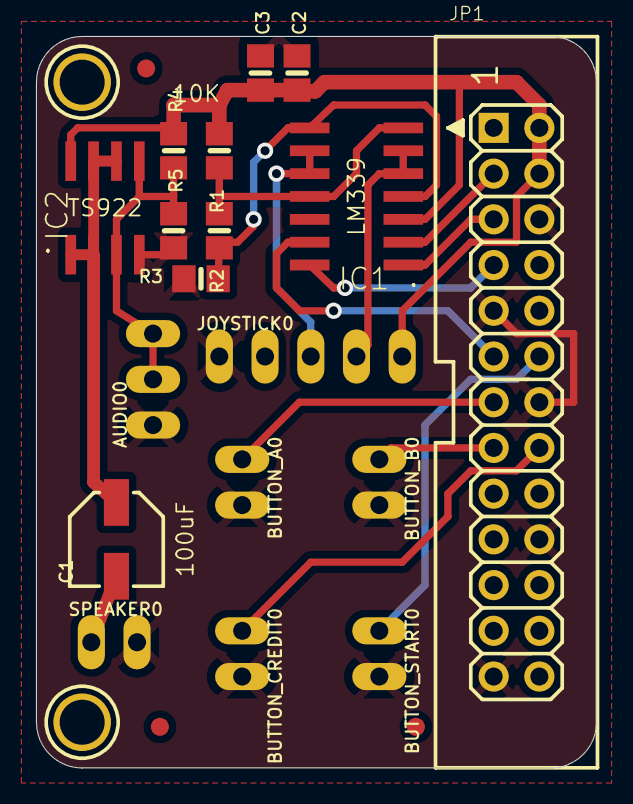
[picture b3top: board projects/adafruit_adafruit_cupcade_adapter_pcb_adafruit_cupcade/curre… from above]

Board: 2 copper layers, 31.1 x 40.6 mm, 24 parts (1 on the bottom side), 17 nets.

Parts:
AUDIO0: 1X03_OVAL
BUTTON_A0: 1X02_OVAL
BUTTON_B0: 1X02_OVAL
BUTTON_CREDIT0: 1X02_OVAL
BUTTON_START0: 1X02_OVAL
C1: 100uF; PANASONIC_C
C2: 10uF; 0805-NO
C3: 0.1uF; 0805-NO
FID1, FID2, FID3: FIDUCIAL""; FIDUCIAL_1MM
IC1: LM339D; SO14
IC2: TS922; SO08
JOYSTICK0: 1X05_OVAL
JP1: RASBERRYPI_IDC
R1, R2, R3, R4, R5: 10K; 0805-NO
SPEAKER0: 8Ohm; 1X02_OVAL
U$1: DRAGON_300MIL
U$2, U$3: MOUNTINGHOLE2.5; MOUNTINGHOLE_2.5_PLATED

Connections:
1/2: AUDIO0.2, AUDIO0.3, IC2.3, IC2.5, R4.1, R5.2
1/3: IC1.4, IC1.8, R2.2, R3.1
2/3: IC1.7, IC1.11, R1.2, R2.1
+5V: C2.1, C3.1, IC1.3, IC2.8, JOYSTICK0.5, JP1.2, JP1.4, R1.1, R4.2
A: BUTTON_A0.1, JP1.13
B: BUTTON_B0.1, JP1.15
CREDIT: BUTTON_CREDIT0.1, JP1.16
DOWN: IC1.14, JP1.7
GND: AUDIO0.1, BUTTON_A0.2, BUTTON_B0.2, BUTTON_CREDIT0.2, BUTTON_START0.2, C2.2, C3.2, IC1.12, IC2.4, JOYSTICK0.1, JP1.6, JP1.9, JP1.14, JP1.20, JP1.25, R3.2, R5.1, SPEAKER0.2
LEFT: IC1.2, JP1.3
unnamed: C1.-, SPEAKER0.1
unnamed: C1.+, IC2.1, IC2.2, IC2.6, IC2.7
RIGHT: IC1.1, JP1.5
START: BUTTON_START0.1, JP1.12
UP: IC1.13, JP1.11
XOUT: IC1.5, IC1.6, JOYSTICK0.4
YOUT: IC1.9, IC1.10, JOYSTICK0.3

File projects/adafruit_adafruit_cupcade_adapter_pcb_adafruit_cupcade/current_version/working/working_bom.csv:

"Id";"Designator";"Footprint";"Quantity";"Designation";"Supplier and ref";
1;"R1,R4,R5,R2,R3";"0805-NO";5;"10K";;;
2;"C1";"PANASONIC_C";1;"100uF";;;
3;"AUDIO0";"1X03_OVAL";1;"";;;
4;"IC1";"SO14";1;"LM339D";;;
5;"U$2,U$3";"MOUNTINGHOLE_2.5_PLATED";2;"MOUNTINGHOLE2.5";;;
6;"IC2";"SO08";1;"TS922";;;
7;"BUTTON_CREDIT0,BUTTON_START0,BUTTON_B0,BUTTON_A0";"1X02_OVAL";4;"";;;
8;"FID1,FID2,FID3";"FIDUCIAL_1MM";3;"FIDUCIAL""";;;
9;"C2";"0805-NO";1;"10uF";;;
10;"JP1";"RASBERRYPI_IDC";1;"";;;
11;"SPEAKER0";"1X02_OVAL";1;"8Ohm";;;
12;"C3";"0805-NO";1;"0.1uF";;;
13;"JOYSTICK0";"1X05_OVAL";1;"";;;
14;"U$1";"DRAGON_300MIL";1;"";;;

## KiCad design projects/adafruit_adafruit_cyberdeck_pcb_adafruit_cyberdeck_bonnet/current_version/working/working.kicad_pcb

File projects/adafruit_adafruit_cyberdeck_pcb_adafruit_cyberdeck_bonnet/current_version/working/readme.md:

# adafruit_cyberdeck_pcb
 
## summary 
* id: adafruit_adafruit_cyberdeck_pcb_adafruit_cyberdeck_bonnet
* user: adafruit
* name: adafruit_cyberdeck_pcb
* board: adafruit_cyberdeck_bonnet
* repo: https://github.com/adafruit/Adafruit-CYBERDECK-PCB

* src_file_repo_sch: 
* src_file_repo_sch_link: https://github.com/adafruit/Adafruit-CYBERDECK-PCB/tree/main/
* full details link: https://github.com/oomlout/oomlout_oomp_project_bot_v_2/tree/main/projects/adafruit_adafruit_cyberdeck_pcb_adafruit_cyberdeck_bonnet/current_version/working  

## schematic  
  
[schematic (pdf)](working_schematic.pdf) 

## pcb  

[board (pdf)](working.pdf)  

## working_bom
| Id | Designator | Footprint | Quantity | Designation | Supplier and ref |  | None | 
| --- | --- | --- | --- | --- | --- | --- | --- | 
| 1 | FID3,FID2,FID1 | FIDUCIAL_1MM | 3 | FIDUCIAL_1MM |  |  | [''] | 
| 2 | CONN3,CONN1 | JST_SH4 | 2 | STEMMA_I2C_QT |  |  | [''] | 
| 3 | R7,R8 | 0603-NO | 2 | 1K |  |  | [''] | 
| 4 | C1,C34 | 0805-NO | 2 | 10uF |  |  | [''] | 
| 5 | @HOLE0,@HOLE2,@HOLE1,@HOLE3 |  | 4 |  |  |  | [''] | 
| 6 | NEOPIX0,SENSE0 | JSTPH3 | 2 | JST PH 3 |  |  | [''] | 
| 7 | U$2 | CYBERDECK_BONNET_TOP | 1 |  |  |  | [''] | 
| 8 | RPI2 | RASPI_2X20_THMSMT_TOP | 1 | RASPBERRYPI_BPLUS_2X20_THMSMT_TOP |  |  | [''] | 
| 9 | D2,D1 | SOD-323 | 2 | 3.6V |  |  | [''] | 
| 10 | SJ1 | SOLDERJUMPER_2WAY_OPEN_NOPASTE | 1 |  |  |  | [''] | 
| 11 | RPI1 | 2X20 | 1 | RASPBERRYPI_BPLUS_IDC |  |  | [''] | 
| 12 | U$1 | CYBERDECK_BONNET_BOT | 1 |  |  |  | [''] | 

## bom_schematic
| Ref | Qnty | Value | Cmp name | Footprint | Description | Vendor | DNP | 
| --- | --- | --- | --- | --- | --- | --- | --- | 
| C1, C34 | 2 | 10uF | CAP_CERAMIC0805-NOOUTLINE | working:0805-NO |  |  |  | 
| CONN1, CONN3 | 2 | STEMMA_I2C_QT | STEMMA_I2C_QT | working:JST_SH4 |  |  |  | 
| D1, D2 | 2 | 3.6V | DIODE-ZENERSOD323 | working:SOD-323 |  |  |  | 
| FID1, FID2, FID3 | 3 | FIDUCIAL_1MM | FIDUCIAL_1MM | working:FIDUCIAL_1MM |  |  |  | 
| NEOPIX0 | 1 | JST PH 3 | CON_JST_PH_3PIN | working:JSTPH3 |  |  |  | 
| R7, R8 | 2 | 1K | RESISTOR_0603_NOOUT | working:0603-NO |  |  |  | 
| RPI1 | 1 | RASPBERRYPI_BPLUS_IDC | RASPBERRYPI_BPLUS_IDC | working:2X20 |  |  |  | 
| RPI2 | 1 | RASPBERRYPI_BPLUS_2X20_THMSMT_TOP | RASPBERRYPI_BPLUS_2X20_THMSMT_TOP | working:RASPI_2X20_THMSMT_TOP |  |  |  | 
| SENSE0 | 1 | JST PH 3 | CON_JST_PH_3PIN | working:JSTPH3 |  |  |  | 
| SJ1 | 1 | SOLDERJUMPER_2WAY | SOLDERJUMPER_2WAY | working:SOLDERJUMPER_2WAY_OPEN_NOPASTE |  |  |  |

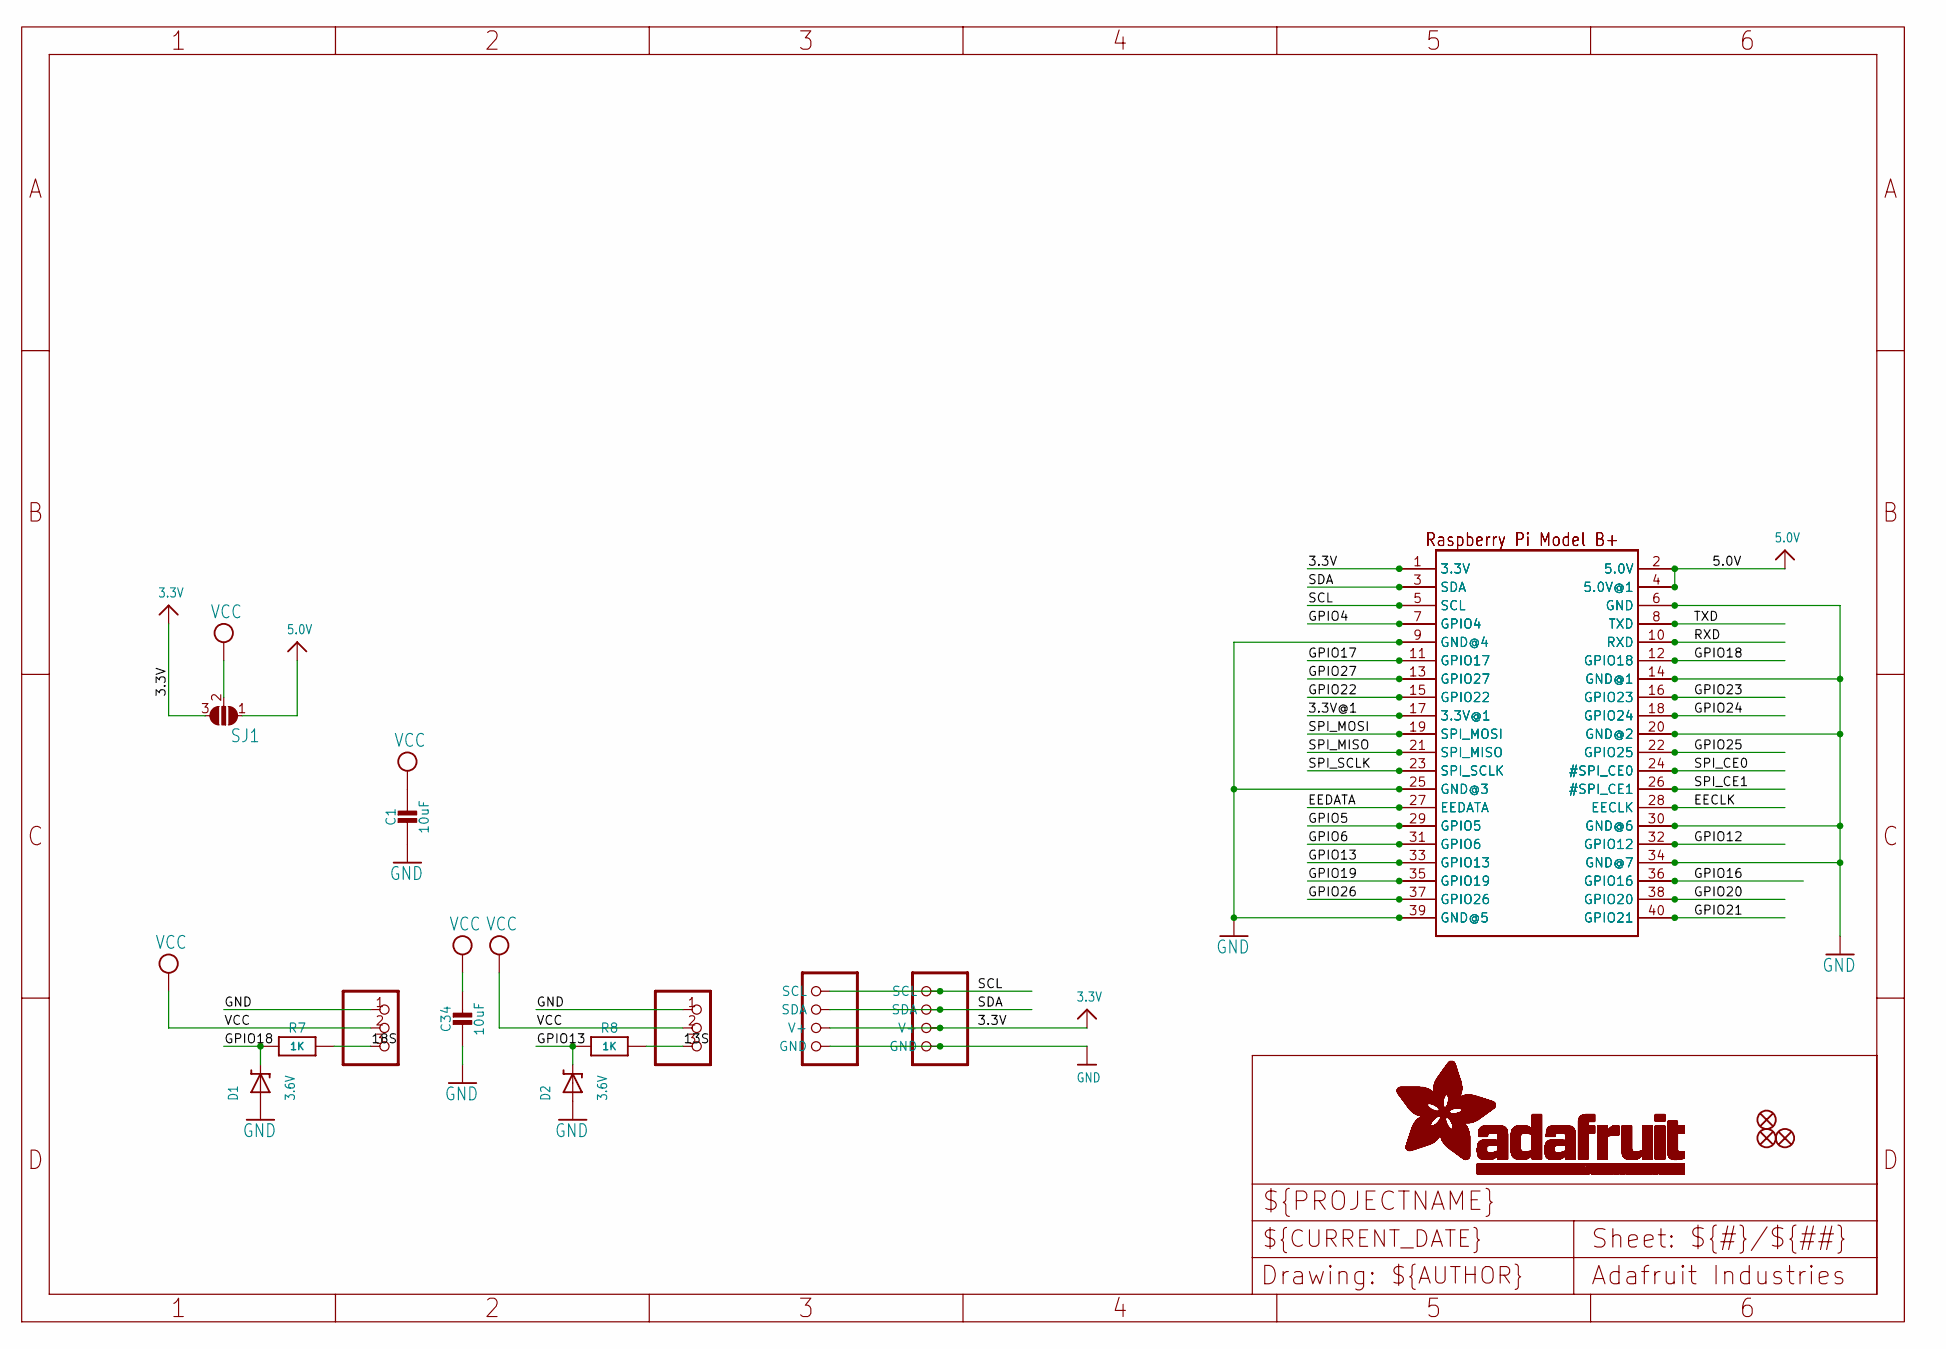
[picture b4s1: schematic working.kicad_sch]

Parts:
C1, C34: 10uF; 0805-NO
CONN1, CONN3: STEMMA_I2C_QT; JST_SH4
D1, D2: 3.6V; SOD-323
FID1, FID2, FID3: FIDUCIAL_1MM
NEOPIX0: JST PH 3; JSTPH3
R7, R8: 1K; 0603-NO
RPI1: RASPBERRYPI_BPLUS_IDC; 2X20
RPI2: RASPBERRYPI_BPLUS_2X20_THMSMT_TOP; RASPI_2X20_THMSMT_TOP
SENSE0: JST PH 3; JSTPH3
SJ1: SOLDERJUMPER_2WAY; SOLDERJUMPER_2WAY_OPEN_NOPASTE

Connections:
3.3V: CONN1.2 (V+), CONN3.2 (V+), RPI1.1 (3.3V), RPI2.1 (3.3V), RPI2.S1 (3.3V), SJ1.3
3.3V@1: RPI1.17 (3.3V@1), RPI2.17 (3.3V@1), RPI2.S17 (3.3V@1)
5.0V: RPI1.2 (5.0V), RPI1.4 (5.0V@1), RPI2.2 (5.0V), RPI2.4 (5.0V@1), RPI2.S2 (5.0V), RPI2.S4 (5.0V@1), SJ1.1
13S: R8.1, SENSE0.3
18S: NEOPIX0.3, R7.1
EECLK: RPI1.28 (EECLK), RPI2.28 (EECLK), RPI2.S28 (EECLK)
EEDATA: RPI1.27 (EEDATA), RPI2.27 (EEDATA), RPI2.S27 (EEDATA)
GND: C1.2, C34.2, CONN1.1 (GND), CONN3.1 (GND), D1.A, D2.A, NEOPIX0.1, RPI1.6 (GND), RPI1.9 (GND@4), RPI1.14 (GND@1), RPI1.20 (GND@2), RPI1.25 (GND@3), RPI1.30 (GND@6), RPI1.34 (GND@7), RPI1.39 (GND@5), RPI2.6 (GND), RPI2.9 (GND@4), RPI2.14 (GND@1), RPI2.20 (GND@2), RPI2.25 (GND@3), RPI2.30 (GND@6), RPI2.34 (GND@7), RPI2.39 (GND@5), RPI2.S6 (GND), RPI2.S9 (GND@4), RPI2.S14 (GND@1), RPI2.S20 (GND@2), RPI2.S25 (GND@3), RPI2.S30 (GND@6), RPI2.S34 (GND@7), RPI2.S39 (GND@5), SENSE0.1
GPIO4: RPI1.7 (GPIO4), RPI2.7 (GPIO4), RPI2.S7 (GPIO4)
GPIO5: RPI1.29 (GPIO5), RPI2.29 (GPIO5), RPI2.S29 (GPIO5)
GPIO6: RPI1.31 (GPIO6), RPI2.31 (GPIO6), RPI2.S31 (GPIO6)
GPIO12: RPI1.32 (GPIO12), RPI2.32 (GPIO12), RPI2.S32 (GPIO12)
GPIO13: D2.C, R8.2, RPI1.33 (GPIO13), RPI2.33 (GPIO13), RPI2.S33 (GPIO13)
GPIO16: RPI1.36 (GPIO16), RPI2.36 (GPIO16), RPI2.S36 (GPIO16)
GPIO17: RPI1.11 (GPIO17), RPI2.11 (GPIO17), RPI2.S11 (GPIO17)
GPIO18: D1.C, R7.2, RPI1.12 (GPIO18), RPI2.12 (GPIO18), RPI2.S12 (GPIO18)
GPIO19: RPI1.35 (GPIO19), RPI2.35 (GPIO19), RPI2.S35 (GPIO19)
GPIO20: RPI1.38 (GPIO20), RPI2.38 (GPIO20), RPI2.S38 (GPIO20)
GPIO21: RPI1.40 (GPIO21), RPI2.40 (GPIO21), RPI2.S40 (GPIO21)
GPIO22: RPI1.15 (GPIO22), RPI2.15 (GPIO22), RPI2.S15 (GPIO22)
GPIO23: RPI1.16 (GPIO23), RPI2.16 (GPIO23), RPI2.S16 (GPIO23)
GPIO24: RPI1.18 (GPIO24), RPI2.18 (GPIO24), RPI2.S18 (GPIO24)
GPIO25: RPI1.22 (GPIO25), RPI2.22 (GPIO25), RPI2.S22 (GPIO25)
GPIO26: RPI1.37 (GPIO26), RPI2.37 (GPIO26), RPI2.S37 (GPIO26)
GPIO27: RPI1.13 (GPIO27), RPI2.13 (GPIO27), RPI2.S13 (GPIO27)
RXD: RPI1.10 (RXD), RPI2.10 (RXD), RPI2.S10 (RXD)
SCL: CONN1.4 (SCL), CONN3.4 (SCL), RPI1.5 (SCL), RPI2.5 (SCL), RPI2.S5 (SCL)
SDA: CONN1.3 (SDA), CONN3.3 (SDA), RPI1.3 (SDA), RPI2.3 (SDA), RPI2.S3 (SDA)
SPI_CE0: RPI1.24 (#SPI_CE0), RPI2.24 (#SPI_CE0), RPI2.S24 (#SPI_CE0)
SPI_CE1: RPI1.26 (#SPI_CE1), RPI2.26 (#SPI_CE1), RPI2.S26 (#SPI_CE1)
SPI_MISO: RPI1.21 (SPI_MISO), RPI2.21 (SPI_MISO), RPI2.S21 (SPI_MISO)
SPI_MOSI: RPI1.19 (SPI_MOSI), RPI2.19 (SPI_MOSI), RPI2.S19 (SPI_MOSI)
SPI_SCLK: RPI1.23 (SPI_SCLK), RPI2.23 (SPI_SCLK), RPI2.S23 (SPI_SCLK)
TXD: RPI1.8 (TXD), RPI2.8 (TXD), RPI2.S8 (TXD)
VCC: C1.1, C34.1, NEOPIX0.2, SENSE0.2, SJ1.2
